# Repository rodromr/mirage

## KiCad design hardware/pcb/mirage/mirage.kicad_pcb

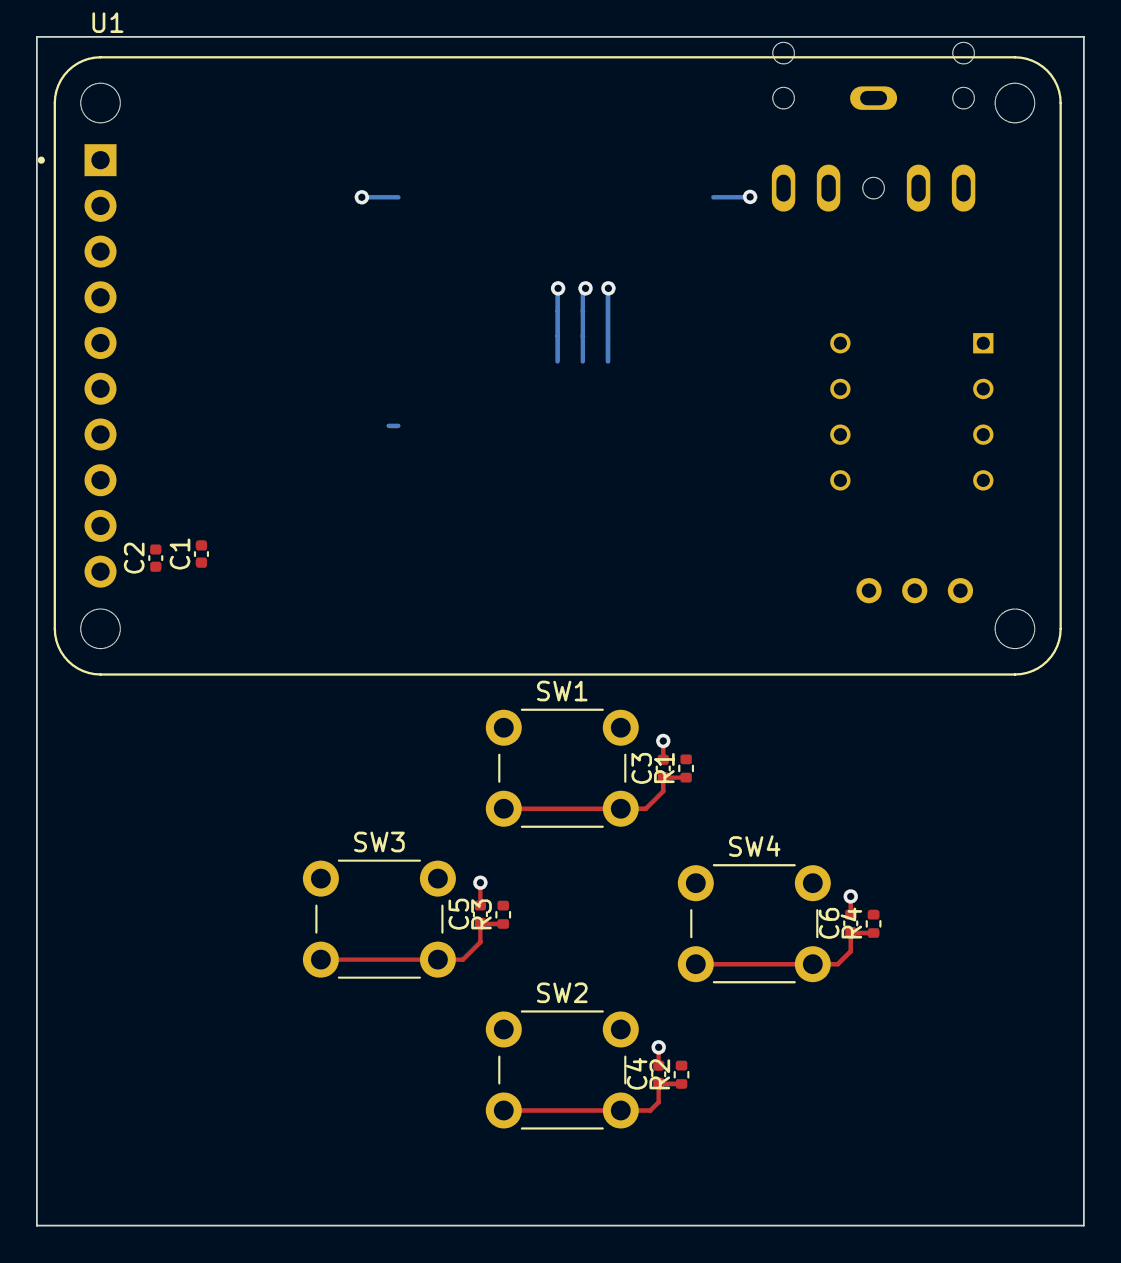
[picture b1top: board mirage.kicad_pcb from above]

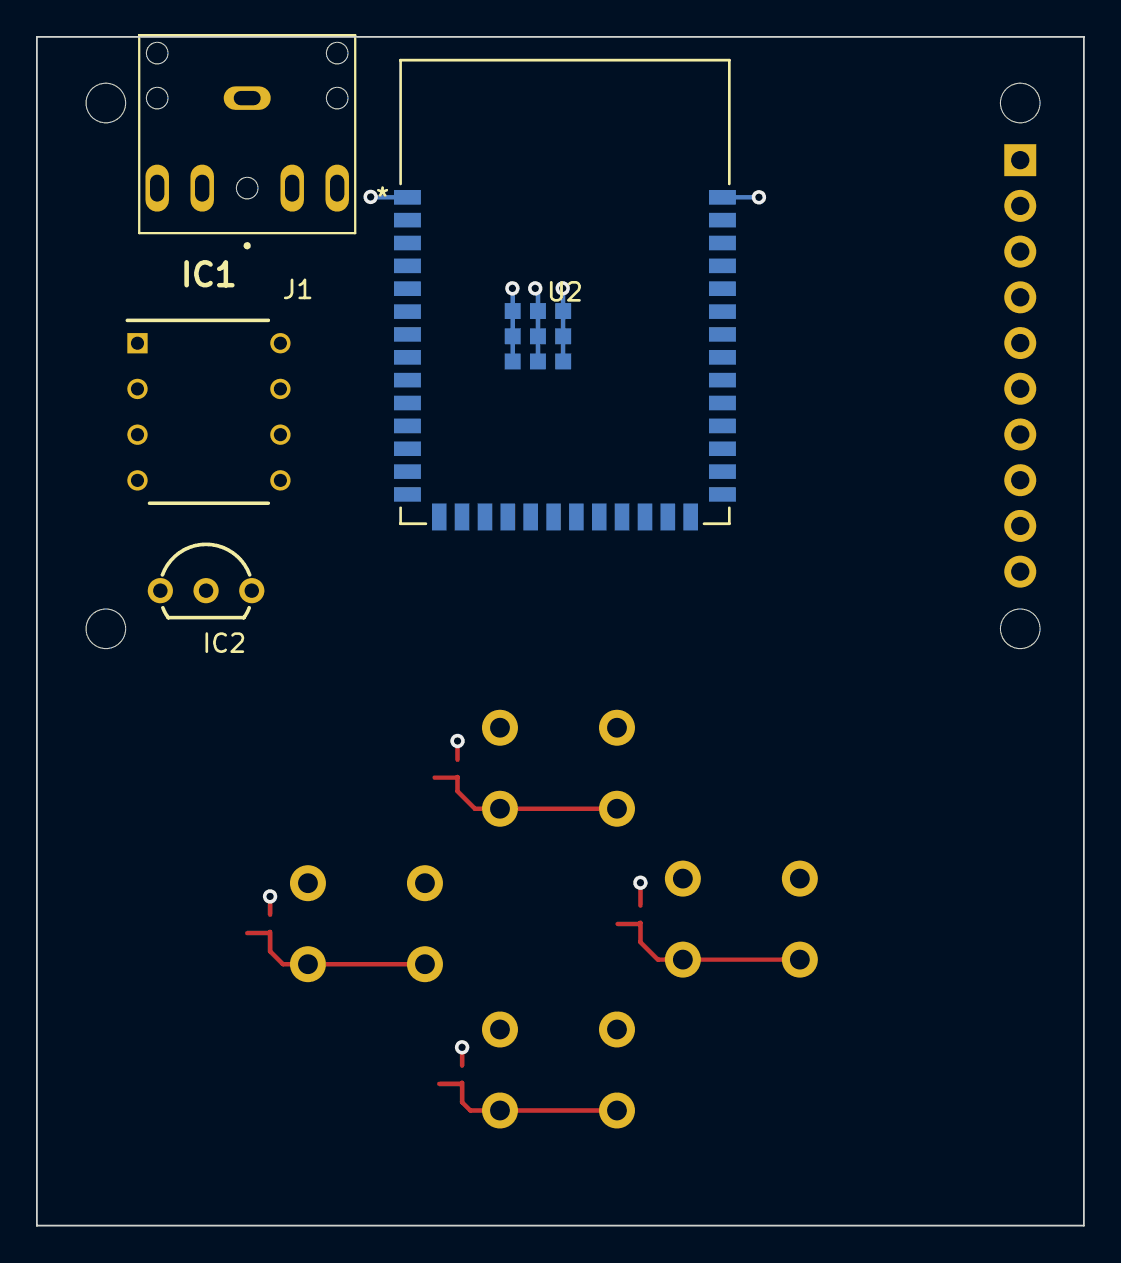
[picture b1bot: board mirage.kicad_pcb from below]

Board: 4 copper layers, 58.2 x 66.0 mm, 19 parts (4 on the bottom side), 13 nets.

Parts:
C1: 100nF; C_0402_1005Metric
C2: 4.7uF; C_0402_1005Metric
C3, C4, C5, C6: 100 nf; C_0402_1005Metric
IC1: TLV5618AIP; ti_TLV5618AIP
IC2: LM4041CILPR; ti_LM4041CILPR
J1: SJ1-3525N; PJ-307
R1, R2, R3, R4: 100K; R_0402_1005Metric
SW1: UP; SW_PUSH_6mm
SW2: DOWN; SW_PUSH_6mm
SW3: LEFT; SW_PUSH_6mm
SW4: RIGHT; SW_PUSH_6mm
U1: Adafruit ST7735R; adafruit_st7735r
U2: ESP32-S3-WROOM-1-N8; ESP32-S3-WROOM-1_EXP

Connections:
+3V3: C1.1, C2.1, R1.2, R2.2, R3.2, R4.2, U1.1 (LITE), U1.9 (VCC), U2.2 (3V3)
/SW_DOWN: C4.1, R2.1, SW2.2
/SW_LEFT: C5.1, R3.1, SW3.2
/SW_RIGHT: C6.1, R4.1, SW4.2
/SW_UP: C3.1, R1.1, SW1.2
/TFT_CS: U1.5 (TFT_CS), U2.5 (IO5)
/TFT_D/C: U1.7 (D/C), U2.38 (IO2)
/TFT_MISO: U1.2 (MISO), U2.30 (IO37)
/TFT_MOSI: U1.4 (MOSI), U2.28 (IO35)
/TFT_RST: U1.8 (RESET), U2.4 (IO4)
/TFT_SCK: U1.3 (SCK), U2.29 (IO36)
/V_REF: IC1.6 (REF), IC2.2
GND: C1.2, C2.2, C3.2, C4.2, C5.2, C6.2, IC1.3 (~CS), IC1.5 (AGND), IC2.3, SW1.1, SW2.1, SW3.1, SW4.1, U1.10 (GND), U2.1 (GND), U2.40 (GND), U2.41 (GND), U2.42 (GND), U2.43 (GND), U2.44 (GND), U2.45 (GND), U2.46 (GND), U2.47 (GND), U2.48 (GND), U2.49 (GND)

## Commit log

2024-08-21 feat: created initial pcb schematic
2024-08-29 feat: added ST7735 driver code and working test code
2024-08-29 feat: temporary pcb/schematic work
2024-08-29 feat: added ignore file
2024-08-29 feat: initial software commit
2024-08-30 fix: changed ST7735 pins to ESP32
2024-08-31 feat: added footprints, schematics, and models
2024-08-31 feat: update ignore file
